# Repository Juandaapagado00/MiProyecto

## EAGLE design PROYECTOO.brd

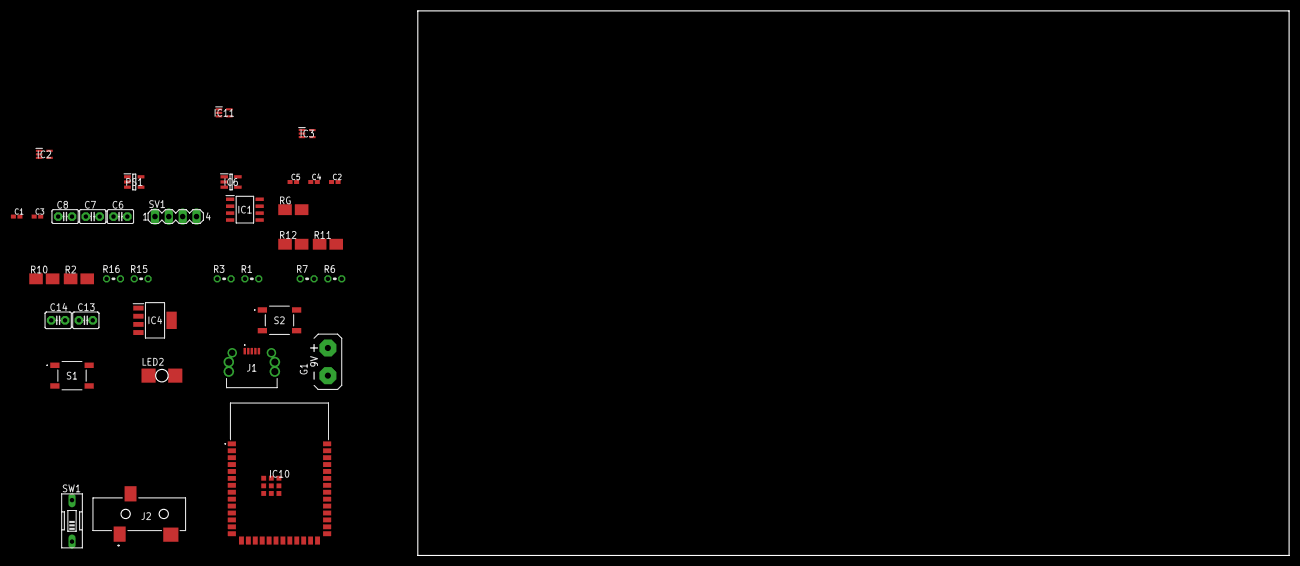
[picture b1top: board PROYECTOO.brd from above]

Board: 2 copper layers, 160.0 x 100.0 mm, 37 parts (0 on the bottom side), 25 nets, no tracks yet.

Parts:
C1, C2, C4, C5: 1u; C0402K
C3: 10u; C0402K
C6, C7, C8: C2.5-2
C13, C14: 10v; C2.5-3
G1: AB9V
IC1: AD8226ARZ; SOIC127P600X175-8N
IC2, IC3, IC11: LMV321AIDCKR; SOT65P210X110-5N
IC4: LP38692MP-3.3_NOPB; SOT150P700X180-5N
IC6: MCP73831T-2ACI_OT; SOT95P270X145-5N
IC10: ESP32-S3-WROOM-1-N16R8; ESP32S3WROOM1N16R8
J1: 204926-1103; 2049261103
J2: SJ-3523-SMT-TR; SJ3523SMTTR
LED2: LAP4-BOTTOM; P47F-BOTTOM
PS1: REF2033AIDDCR; SOT95P280X110-5N
R1, R3: 1.6k; 0204V
R2: 10K; SMK
R6, R7: 320k; 0204V
R10, R11: 12K; SMK
R12: 1k; SMK
R15: 220; 0204V
R16: 2k; 0204V
RG: 50; SMK
S1, S2: TS18-5-17-SL-160-SMT-TR; TS18517SL160SMTTR
SV1: MA04-1
SW1: EDG-01

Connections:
+BATT: C13.1, G1.+, IC6.3, SW1.2
GND: C1.2, C3.2, C6.1, C7.1, C8.2, C13.2, C14.2, G1.-, IC1.5, IC2.2, IC3.2, IC4.5, IC6.2, IC10.1, IC10.40, IC10.41, IC10.42, IC10.43, IC10.44, IC10.45, IC10.46, IC10.47, IC10.48, IC10.49, IC11.2, J1.5, J1.MH1, J1.MH2, J1.MH3, J1.MH4, J1.MH5, J1.MH6, PS1.2, R6.2, R16.1, S1.3, S2.1, SV1.1
unnamed: IC1.1, J2.2
unnamed: IC1.2, RG.1
unnamed: IC1.3, RG.2
unnamed: C1.1, IC2.1, R3.1
unnamed: C2.1, R1.1, R3.2
unnamed: C7.2, IC10.3, R10.1, S1.1
unnamed: C2.2, C4.1, IC2.3, IC2.4
unnamed: C4.2, C5.1, R7.2
unnamed: C5.2, IC3.1, R6.1
unnamed: IC3.3, IC3.4, R7.1
unnamed: IC1.4, J2.3
unnamed: IC4.1, IC4.4, SW1.1
unnamed: IC6.1, R15.1
unnamed: LED2.C, R15.2
unnamed: IC6.5, R16.2
unnamed: C8.1, IC10.27, R11.1, S2.3
unnamed: IC11.3, R2.2, R12.1
unnamed: IC11.4, R2.1
OUT_1: IC1.7, R1.2
SCL: IC10.36, SV1.3
SDA: IC10.33, SV1.4
VCC: C3.1, C6.2, C14.1, IC1.8, IC2.5, IC3.5, IC4.3, IC6.4, IC10.2, IC11.5, J1.1, LED2.A, PS1.3, PS1.4, R10.2, R11.2, SV1.2
VSS: IC1.6, IC11.1, PS1.1

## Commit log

2025-03-28 Commit inicial
2025-03-28 Estructura inicial del proyecto
2025-03-28 Añadida funcionalidad A
2025-04-04 Avance PCB
    Amplificador de instrumentaciòn, filtro pasa banda, regulador de voltaje y puerto de carga
2025-04-11 Correcciones del profesor
2025-05-05 Mas correcciones del profesor
